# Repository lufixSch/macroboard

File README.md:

# Macroboard

DIY Macro keyboard with pedal support based on Arduino Micro.

This project contains the build files and firmware for an plug and play macro keyboard. It doesn't require any third party software on your PC instead it makes use of the **F13** - **F24** keys which are usually unused. The (optional) mode switch allows a secondary layer of macro keys (**F1** - **F12**).
In addition the board has a port for a sustain pedal from a E-Piano with automatic polarity detection. The design includes a separate mode switch for the pedal as well as a manual polarity switch to allow more exceptional use cases like push to mute in games where only push to talk is supported.

## Circuit

Contains the PCB design for the board based around an Arduino Micro development board.

Not all switches/keys need to be populated. You can omit _Special Key_, _Mode Switch_ and _Special Switch 1/2_ based on your needs and disable the corresponding features in the firmware.

## Firmware

Contains the Arduino sketch which should be flashed onto the Arduino Micro. The firmware relies on the Arduino Keyboard library and can be configured using macros in the `settings.h`.

## Case

Contains the FreeCAD as well as STL files for a simple printable enclosure for the _Macroboard_.

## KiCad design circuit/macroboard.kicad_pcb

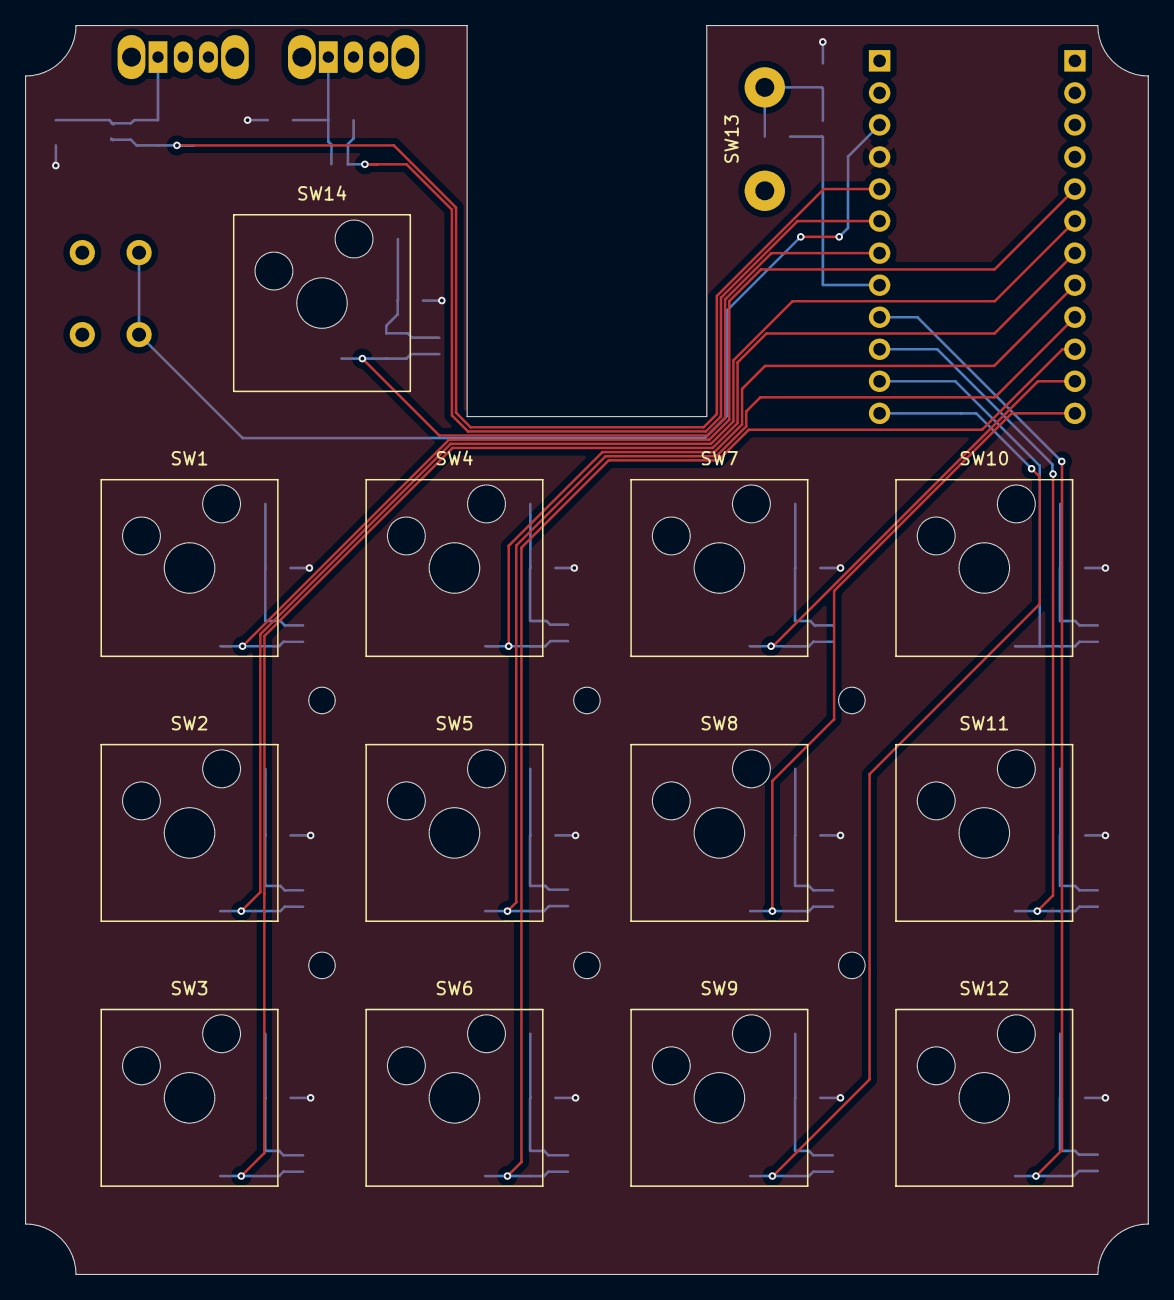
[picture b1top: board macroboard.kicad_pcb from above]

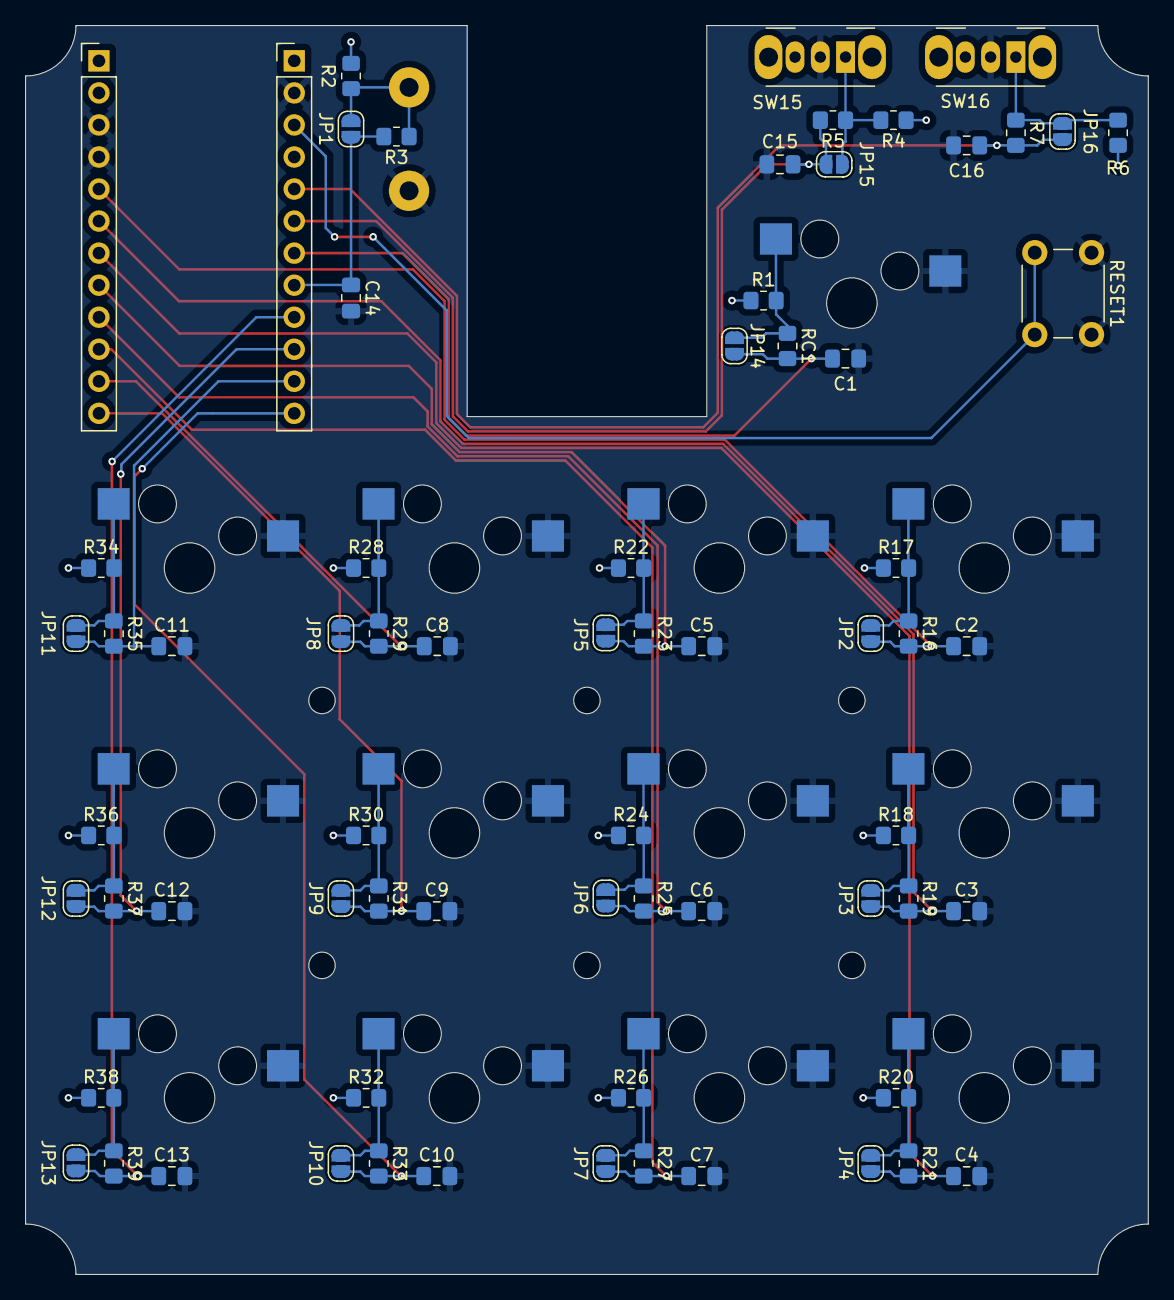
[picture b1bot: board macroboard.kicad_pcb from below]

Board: 2 copper layers, 89.0 x 99.0 mm, 88 parts (68 on the bottom side), 35 nets.

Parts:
C1, C2, C3, C4, C5, C6, C7, C8, C9, C10, C11, C12, C13, C14, C15, C16: 10u; C_0805_2012Metric_Pad1.18x1.45mm_HandSolder
H1, H2, H3, H4, H5, H6: MountingHole; MountingHole_2.1mm
JP1, JP2, JP3, JP4, JP5, JP6, JP7, JP8, JP9, JP10, JP11, JP12, JP13, JP14, JP15, JP16: Jumper_2_Open; SolderJumper-2_P1.3mm_Open_RoundedPad1.0x1.5mm
R1, R2, R4, R6, R17, R18, R20, R22, R24, R26, R28, R30, R32, R34, R36, R38: 10k; R_0805_2012Metric_Pad1.20x1.40mm_HandSolder
R3, R5, R7, R16, R19, R21, R23, R25, R27, R29, R31, R33, R35, R37, R39: 1k; R_0805_2012Metric_Pad1.20x1.40mm_HandSolder
RC1: 1k; R_0805_2012Metric_Pad1.20x1.40mm_HandSolder
RESET1: SW_Push; SW_PUSH_6mm
SW1, SW2, SW3, SW4, SW5, SW6, SW7, SW8, SW9, SW10, SW11, SW12, SW14: CherryMX; CherryMX_1.00u_KailhSocket
SW13: SW_Push; AUX Jack 6.3mm External
SW15, SW16: SW_SPDT; SW_Slide_SPDT_Angled_CK_OS102011MA1Q
U1: ATmega32U4-A; Arduino Pro Micro

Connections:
/Debounce13/IN: JP1.1 (A), R2.2, R3.1, SW13.2
/Debounce15/IN: JP15.1 (A), R4.2, R5.1, SW15.1 (A)
/Debounce16/IN: JP16.1 (A), R6.2, R7.1, SW16.1 (A)
/KEY1: C2.1, JP2.2 (B), R16.2, U1.19 (PD1)
/KEY2: C3.1, JP3.2 (B), R19.2, U1.18 (PD0)
/KEY3: C4.1, JP4.2 (B), R21.2, U1.25 (PD4)
/KEY4: C5.1, JP5.2 (B), R23.2, U1.31 (PC6)
/KEY5: C6.1, JP6.2 (B), R25.2, U1.27 (PD7)
/KEY6: C7.1, JP7.2 (B), R27.2, U1.1 (PE6)
/KEY7: C8.1, JP8.2 (B), R29.2, U1.28 (PB4)
/KEY8: C9.1, JP9.2 (B), R31.2, U1.29 (PB5)
/KEY9: C10.1, JP10.2 (B), R33.2, U1.30 (PB6)
/KEY10: C11.1, JP11.2 (B), R35.2, U1.10 (PB2)
/KEY11: C12.1, JP12.2 (B), R37.2, U1.11 (PB3)
/KEY12: C13.1, JP13.2 (B), R39.2, U1.9 (PB1)
/MODE_SWITCH: C1.1, JP14.2 (B), RC1.2, U1.37 (PF6)
/SPECIAL_KEY: C14.1, JP1.2 (B), R3.2, U1.36 (PF7)
/SPECIAL_SWITCH_1: C15.1, JP15.2 (B), R5.2, U1.38 (PF5)
/SPECIAL_SWITCH_2: C16.1, JP16.2 (B), R7.2, U1.39 (PF4)
/Switch1/Debounce1/IN: JP2.1 (A), R16.1, R17.2, SW1.2
/Switch2/Debounce1/IN: JP3.1 (A), R18.2, R19.1, SW2.2
/Switch3/Debounce1/IN: JP4.1 (A), R20.2, R21.1, SW3.2
/Switch4/Debounce1/IN: JP5.1 (A), R22.2, R23.1, SW4.2
/Switch5/Debounce1/IN: JP6.1 (A), R24.2, R25.1, SW5.2
/Switch6/Debounce1/IN: JP7.1 (A), R26.2, R27.1, SW6.2
/Switch7/Debounce1/IN: JP8.1 (A), R28.2, R29.1, SW7.2
/Switch8/Debounce1/IN: JP9.1 (A), R30.2, R31.1, SW8.2
/Switch9/Debounce1/IN: JP10.1 (A), R32.2, R33.1, SW9.2
/Switch10/Debounce1/IN: JP11.1 (A), R34.2, R35.1, SW10.2
/Switch11/Debounce1/IN: JP12.1 (A), R36.2, R37.1, SW11.2
/Switch12/Debounce1/IN: JP13.1 (A), R38.2, R39.1, SW12.2
/Switch13/Debounce1/IN: JP14.1 (A), R1.2, RC1.1, SW14.2
GND: C1.2, C2.2, C3.2, C4.2, C5.2, C6.2, C7.2, C8.2, C9.2, C10.2, C11.2, C12.2, C13.2, C14.2, C15.2, C16.2, RESET1.1, SW1.1, SW2.1, SW3.1, SW4.1, SW5.1, SW6.1, SW7.1, SW8.1, SW9.1, SW10.1, SW11.1, SW12.1, SW13.1, SW14.1, SW15.2 (B), SW16.2 (B), U1.5 (UGND), U1.15 (GND)
unnamed: RESET1.2, U1.13 (~RESET)
VCC: R1.1, R2.1, R4.1, R6.1, R17.1, R18.1, R20.1, R22.1, R24.1, R26.1, R28.1, R30.1, R32.1, R34.1, R36.1, R38.1, U1.14 (VCC)

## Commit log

2025-04-27 add circuit design
2025-04-27 add cherry mx lib submodule, add basic circuit
2025-04-27 add basic pcb layout (no routing)
2025-04-27 add initial firmware
2025-04-27 remove unused files/directories
2025-04-27 comment code
2025-04-30 move firmware to Arduino Sketch (Issue with PIO), fix minor issues
2025-04-30 add reusable debounce circuit with solder jumper
2025-04-30 clean up sketch, add explicit settings header file
2025-04-30 add custom footprints, improve layout
2025-05-03 add special switches, add routing
2025-05-05 add reset switch
2025-05-05 add gerber files
2025-05-12 add special key mode and polarity switch, add special key auto polarity
2025-05-12 fix wrong pin distance on Arduino micro footprint
2025-05-18 add case
2025-05-18 improve switch positioning
2025-05-19 improve case stability and printability
